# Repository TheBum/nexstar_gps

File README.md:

# SkySync GPS clone
 
A project to build an open source Celestron SkySync GPS compatible unit. This variant includes a 128x32 pixel SSD1306 OLED display for showing position, time, and satellite information.
 
Forked from ForestTree's fork of the fantastic project by bebrown (https://github.com/bebrown/nexstar_gps).
 
## Goals
 
Construct a SkySync-compatible unit for attaching a GPS to Celestron mounts that don't already have a GPS, such as the CGEM or AVX.
 
## Parts
 
To build this, you will need:
 
* A GPS module, such as the uBlox NEO-6M. Commonly used by hoobyists for their quadcopters.
  Available for about $16.
 
* A small Arduino, such as the Pro Mini (5V version). Clones available for about $3.
 
* A TTL serial-to-USB adapter for programming the Arduino (if it does not have an on-board
  USB port already). Available for about $3.
 
* A 128x32 pixel (or larger) SSD1306 I2C OLED display.
 
## Construction
 
See [schematics diagram](eagle-Nano/Nano-schematic.png).
 
## Libraries
 
You will need to install the following libraries:
 
* TinyGPS++, available from http://arduiniana.org/libraries/tinygpsplus/.
 
* SSD1306Ascii, available through the Arduino Library Manager.
 
Also needed are the following libraries built in to the Arduino IDE:
 
* SoftwareSerial
 
* Wire
 
## Additional info
 
See this links for more info about Celestron mounts, AUX port, wiring and communication protocol:
 
https://www.nexstarsite.com/download/manuals/NexStarCommunicationProtocolV1.2.zip
https://sites.google.com/site/wayneholder/nexstar-direct-telescope-mount-control
https://www.nexstarsite.com/download/CelestronAS_PCinterface.pdf
http://www.paquettefamily.ca/nexstar/NexStar_AUX_Commands_10.pdf

The eagle-Nano folder contains the EAGLE design files for the schematic and board, as well as a zip archive ready for upload to a PCB service (e.g. https://jlcpcb.com).
 
## Attention
 
Be attentive during construction and testing your device!!! You can easy destroy the motherboard in your astro mount.

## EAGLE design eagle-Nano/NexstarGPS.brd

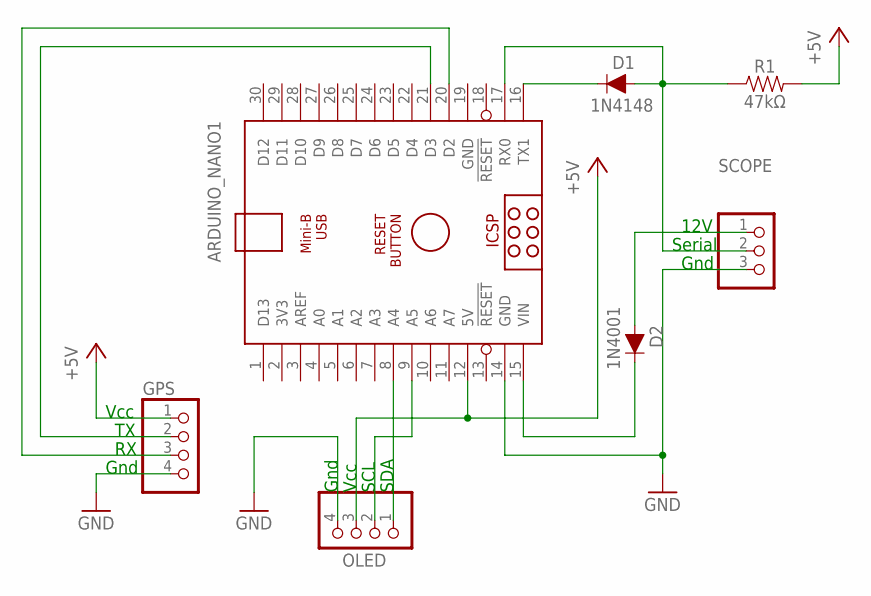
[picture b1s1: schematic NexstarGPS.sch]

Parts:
ARDUINO_NANO1: ARDUINO_NANO
D1: 1N4148; DIODE-1N4148
D2: 1N4001; DIODE-1N4001
GPS: PINHD-1X4; 1X04
OLED: PINHD-1X4; 1X04
R1: 47kΩ; AXIAL-0.3
SCOPE: PINHD-1X3; 1X03

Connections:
5V: ARDUINO_NANO1.12 (5V), GPS.1, OLED.3, R1.P$2 (2)
12V: ARDUINO_NANO1.15 (VIN), D2.C
GND: ARDUINO_NANO1.14 (GND), ARDUINO_NANO1.19 (GND), GPS.4, OLED.4, SCOPE.3
GPSRX: ARDUINO_NANO1.20 (D2), GPS.3
GPSTX: ARDUINO_NANO1.21 (D3), GPS.2
unnamed: D2.A, SCOPE.1
NANOTX1: ARDUINO_NANO1.16 (TX1), D1.C
OLEDSCL: ARDUINO_NANO1.9 (A5), OLED.2
OLEDSDA: ARDUINO_NANO1.8 (A4), OLED.1
SCOPESERIAL: ARDUINO_NANO1.17 (RX0), D1.A, R1.P$1 (1), SCOPE.2

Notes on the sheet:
Vcc
Gnd
Serial
12V
SDA
SCL

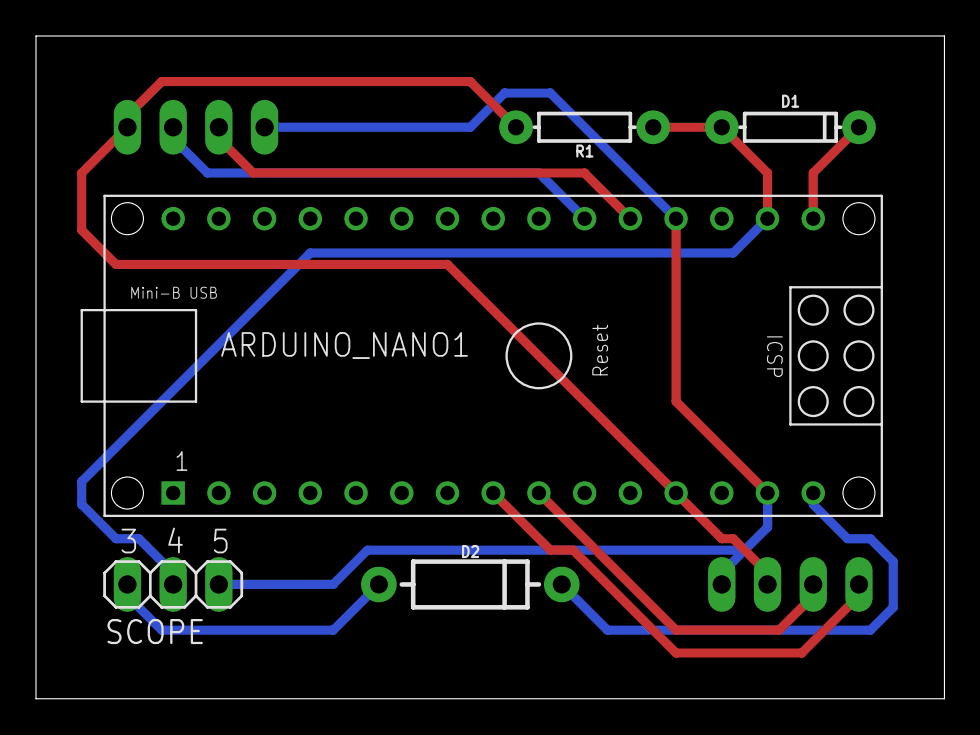
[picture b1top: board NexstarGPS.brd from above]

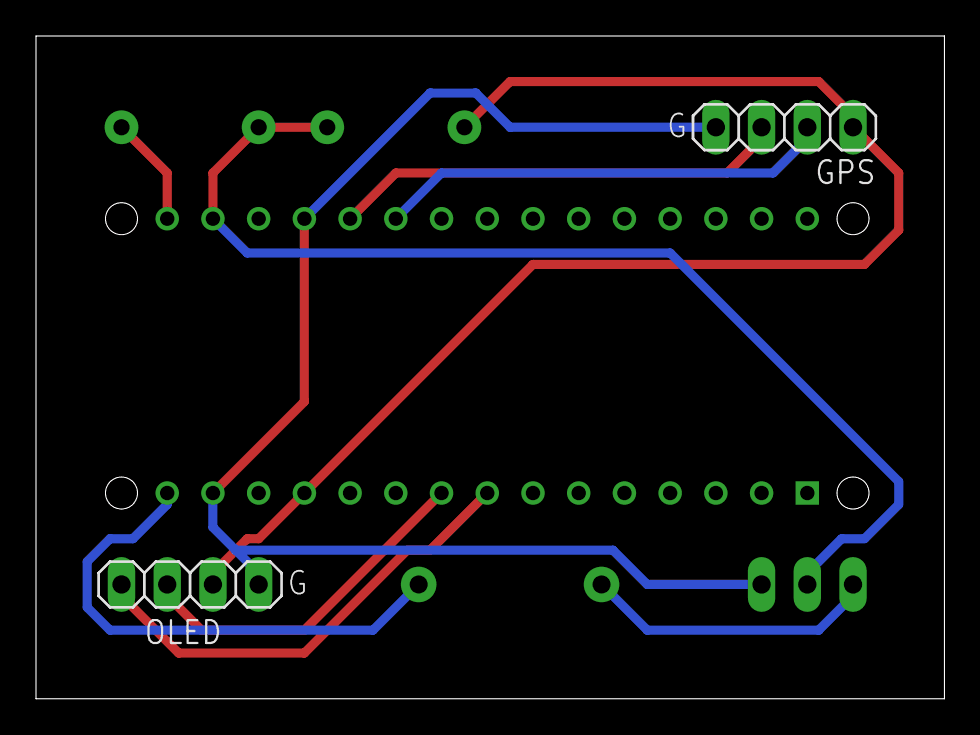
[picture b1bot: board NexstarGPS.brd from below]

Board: 2 copper layers, 50.5 x 36.8 mm, 7 parts (2 on the bottom side), 10 nets.

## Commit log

2019-04-15 Added support for an SSD1306 128x32 OLED display
2019-04-16 Updated for additional attribution and to add info related to the OLED module
2019-04-17 EAGLE schematic and board files
    This is for an Arduino Nano implementation. Also included are a schematic image for easy viewing and a zip archive that can be uploaded to a PCB service.
2019-04-17 EAGLE info and new schematic link

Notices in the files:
parts and their libraries:
SparkFun-DiscreteSemi: Licensing: Creative Commons ShareAlike 4.0 International - https://creativecommons.org/licenses/by-sa/4.0
